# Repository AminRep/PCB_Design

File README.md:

# PCB_Design
Various PCB CAD models developed using KiCad software for educational and personal purposes.
## STM32 PCB Design
This is a custom PCB design for the microcontroller STM32F103C8T6, intended to assist in embedded systems studies. The design was realized from a detailed schematic using KiCad to the design of the PCB layout in a compact way. It provides a solid board on which to perform programming and prototyping with the STM32 processor, among other applications. Much attention was paid to ensuring that the design is easy for beginners to follow while still being highly functional.

## Self-Balancing Robot PCB
This PCB design is tailored for a self-balancing robot. It integrates key components like the L298N motor driver, MPU6050 gyroscope and accelerometer, and an Arduino Nano microcontroller. The layout provides a compact and efficient way to control motors, balancing algorithms, and sensor integration.

### Features:
* Motor Control: L298N driver to manage two DC motors.
* Sensor Input: MPU6050 for real-time balance adjustments.
* Microcontroller: Arduino Nano compatibility for seamless programming and control.
* Power Management: Includes regulators for stable operation.

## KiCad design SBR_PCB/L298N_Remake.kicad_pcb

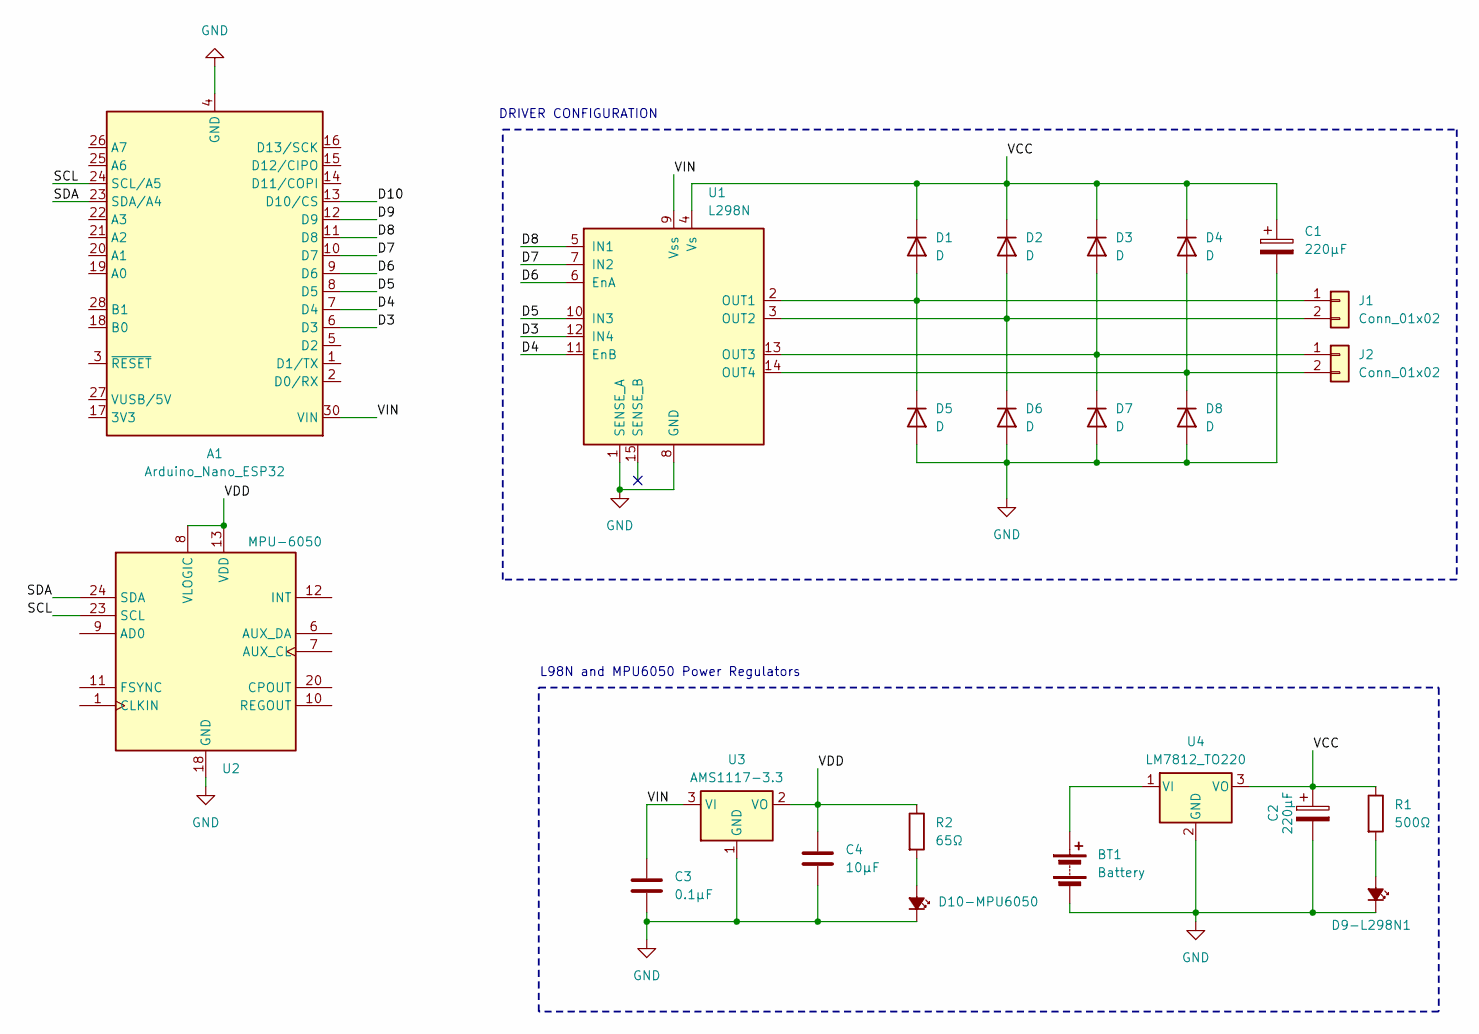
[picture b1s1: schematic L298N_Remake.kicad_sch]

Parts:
A1: Arduino_Nano_ESP32; Arduino_Nano
BT1: Battery; BatteryHolder_Bulgin_BX0036_1xC
C1, C2: 220µF; CP_Radial_D8.0mm_P2.50mm
C3: 0.1µF; C_Axial_L3.8mm_D2.6mm_P7.50mm_Horizontal
C4: 10µF; CP_Radial_D4.0mm_P1.50mm
D1, D2, D3, D4, D5, D6, D7, D8: D; D_A-405_P2.54mm_Vertical_AnodeUp
D9-L298N1, D10-MPU6050: LED_Small_Filled; LED_D3.0mm
J1, J2: Conn_01x02; TerminalBlock_Phoenix_MKDS-1,5-2-5.08_1x02_P5.08mm_Horizont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
R1: 500Ω; R_Axial_DIN0204_L3.6mm_D1.6mm_P7.62mm_Horizontal
R2: 65Ω; R_Axial_DIN0204_L3.6mm_D1.6mm_P5.08mm_Horizontal
U1: L298N; Multiwatt15_V_STM
U2: MPU-6050; InvenSense_QFN-24_4x4mm_P0.5mm
U3: AMS1117-3.3; SOT-223-3_TabPin2
U4: LM7812_TO220; TO-220-3_Vertical

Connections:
/D3: A1.6 (D3), U1.12 (IN4)
/D4: A1.7 (D4), U1.11 (EnB)
/D5: A1.8 (D5), U1.10 (IN3)
/D6: A1.9 (D6), U1.6 (EnA)
/D7: A1.10 (D7), U1.7 (IN2)
/D8: A1.11 (D8), U1.5 (IN1)
/D9: A1.12 (D9)
/D10: A1.13 (D10/CS)
/SCL: A1.24 (SCL/A5), U2.23 (SCL)
/SDA: A1.23 (SDA/A4), U2.24 (SDA)
/VCC: C1.1, C2.1, D1.1 (K), D2.1 (K), D3.1 (K), D4.1 (K), R1.1, U1.4 (Vs), U4.3 (VO)
/VDD: C4.1, R2.1, U2.8 (VLOGIC), U2.13 (VDD), U3.2 (VO)
/VIN: A1.30 (VIN), C3.1, U1.9 (Vss), U3.3 (VI)
GND: A1.4 (GND), A1.29 (GND), BT1.2 (-), C1.2, C2.2, C3.2, C4.2, D5.2 (A), D6.2 (A), D7.2 (A), D8.2 (A), D9-L298N1.1 (K), D10-MPU6050.1 (K), U1.1 (SENSE_A), U1.8 (GND), U2.18 (GND), U3.1 (GND), U4.2 (GND)
unnamed: BT1.1 (+), U4.1 (VI)
unnamed: D1.2 (A), D5.1 (K), J1.1, U1.2 (OUT1)
unnamed: D2.2 (A), D6.1 (K), J1.2, U1.3 (OUT2)
unnamed: D3.2 (A), D7.1 (K), J2.1, U1.13 (OUT3)
unnamed: D4.2 (A), D8.1 (K), J2.2, U1.14 (OUT4)
unnamed: D9-L298N1.2 (A), R1.2
unnamed: D10-MPU6050.2 (A), R2.2

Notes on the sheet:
L98N and MPU6050 Power Regulators
DRIVER CONFIGURATION

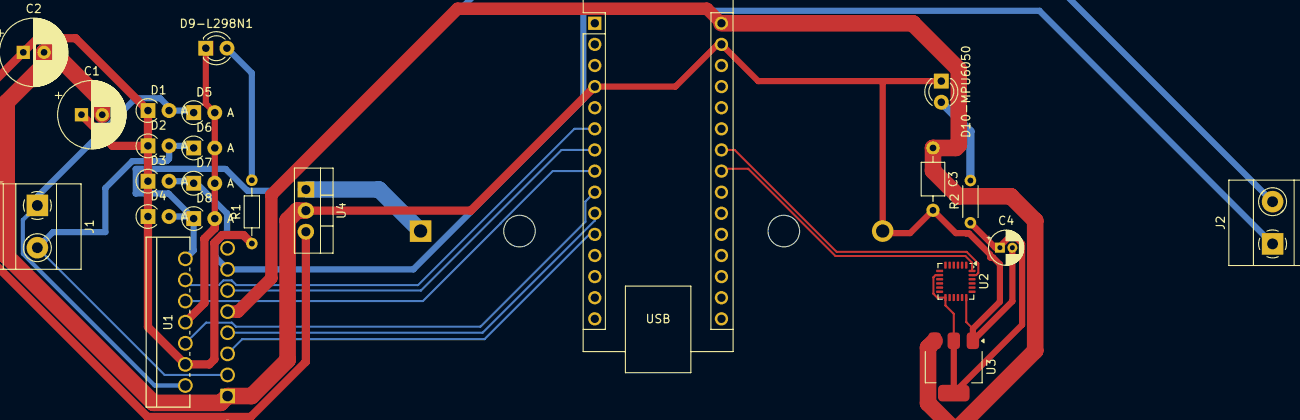
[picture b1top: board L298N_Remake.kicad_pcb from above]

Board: 2 copper layers, 24 parts (1 on the bottom side), 19 nets.

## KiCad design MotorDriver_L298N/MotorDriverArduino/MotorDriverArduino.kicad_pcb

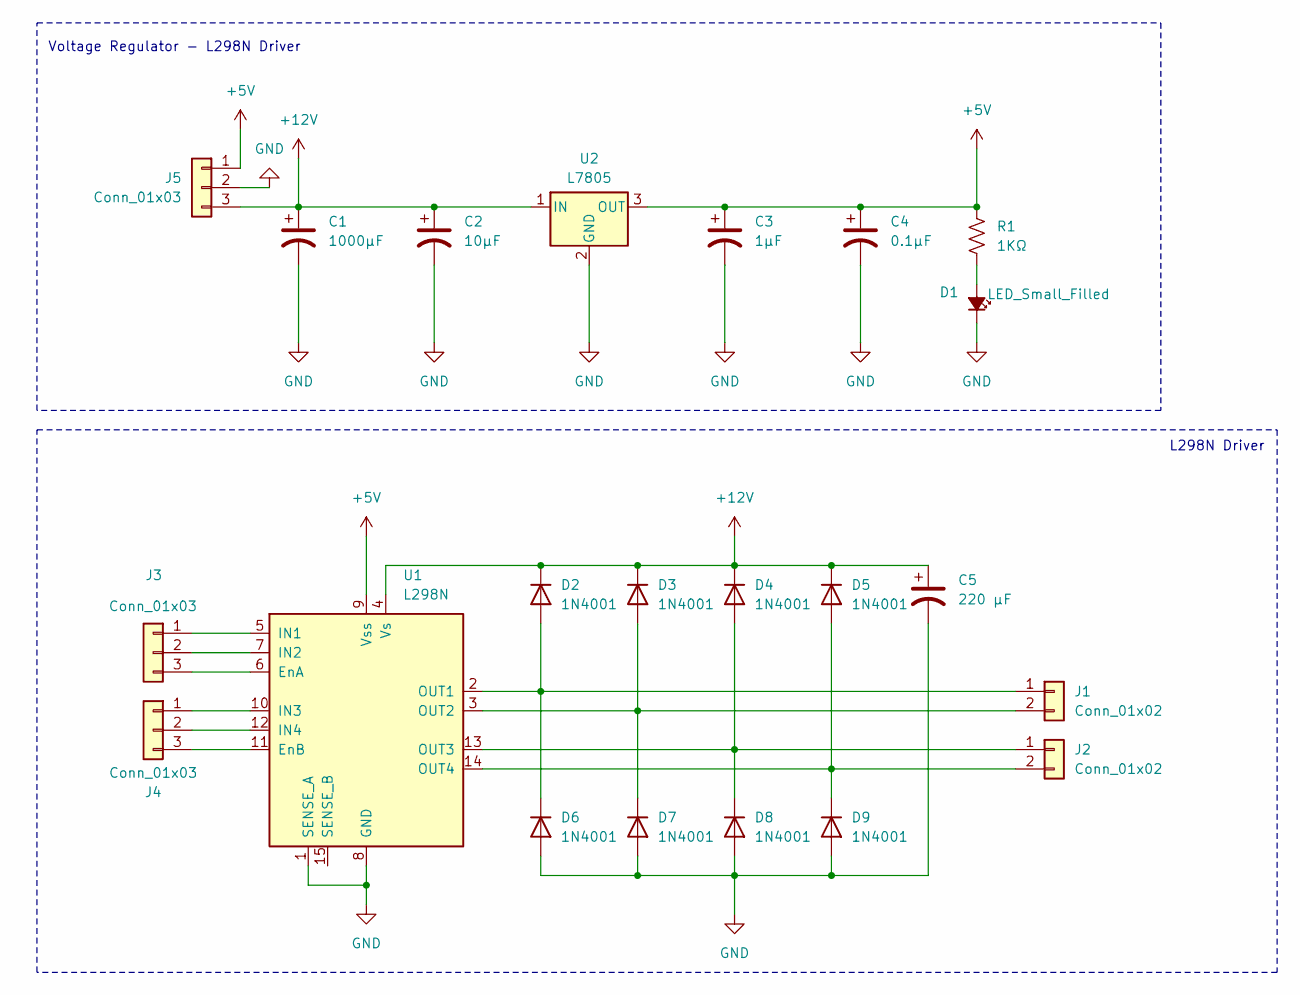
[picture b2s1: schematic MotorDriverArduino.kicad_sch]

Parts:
C1: 1000µF; CP_Radial_D5.0mm_P2.50mm
C2: 10µF; CP_Radial_D4.0mm_P1.50mm
C3: 1µF; C_0402_1005Metric
C4: 0.1µF; C_0402_1005Metric
C5: 220 µF; C_0805_2012Metric
D1: LED_Small_Filled; LED_0402_1005Metric_Pad0.77x0.64mm_HandSolder
D2, D3, D4, D5, D6, D7, D8, D9: 1N4001; D_0603_1608Metric_Pad1.05x0.95mm_HandSolder
J1, J2: Conn_01x02; TerminalBlock_Phoenix_MKDS-1,5-2_1x02_P5.00mm_Horizontal
J3, J4: Conn_01x03; PinSocket_1x03_P1.00mm_Vertical
J5: Conn_01x03; TerminalBlock_Phoenix_MKDS-1,5-3-5.08_1x03_P5.08mm_Horizont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
R1: 1KΩ; R_0805_2012Metric
U1: L298N; Multiwatt15_V_STM
U2: L7805; TO-262-3-1EP_Horizontal_TabDown

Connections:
+5V: C3.1, C4.1, J5.1, R1.1, U1.9 (Vss), U2.3 (OUT)
+12V: C1.1, C2.1, C5.1, D2.1 (K), D3.1 (K), D4.1 (K), D5.1 (K), J5.3, U1.4 (Vs), U2.1 (IN)
GND: C1.2, C2.2, C3.2, C4.2, C5.2, D1.1 (K), D6.2 (A), D7.2 (A), D8.2 (A), D9.2 (A), J5.2, U1.1 (SENSE_A), U1.8 (GND), U2.2 (GND)
unnamed: D1.2 (A), R1.2
unnamed: D2.2 (A), D6.1 (K), J1.1, U1.2 (OUT1)
unnamed: D3.2 (A), D7.1 (K), J1.2, U1.3 (OUT2)
unnamed: D4.2 (A), D8.1 (K), J2.1, U1.13 (OUT3)
unnamed: D5.2 (A), D9.1 (K), J2.2, U1.14 (OUT4)
unnamed: J3.1, U1.5 (IN1)
unnamed: J3.2, U1.7 (IN2)
unnamed: J3.3, U1.6 (EnA)
unnamed: J4.1, U1.10 (IN3)
unnamed: J4.2, U1.12 (IN4)
unnamed: J4.3, U1.11 (EnB)

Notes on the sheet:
L298N Driver
Voltage Regulator - L298N Driver

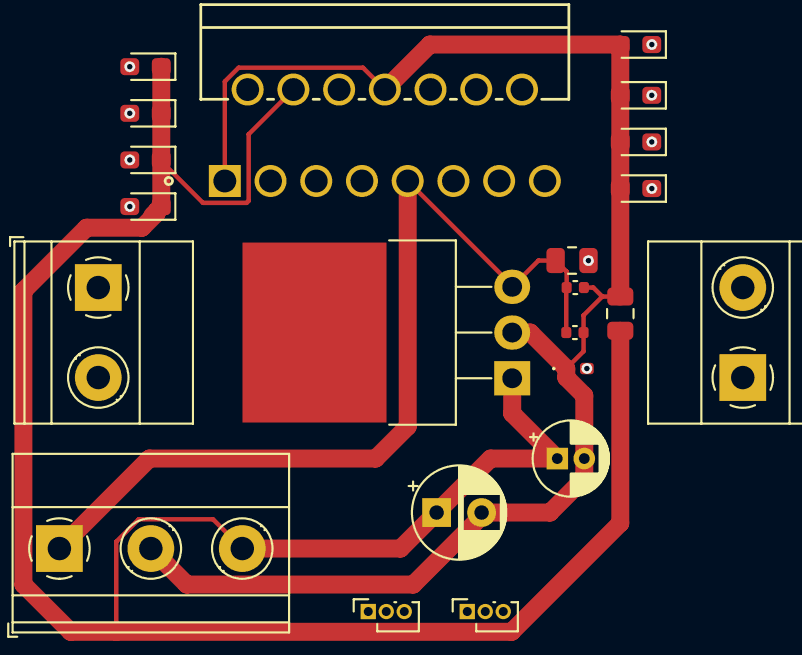
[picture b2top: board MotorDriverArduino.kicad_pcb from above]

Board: 4 copper layers, 22 parts (0 on the bottom side), 14 nets.

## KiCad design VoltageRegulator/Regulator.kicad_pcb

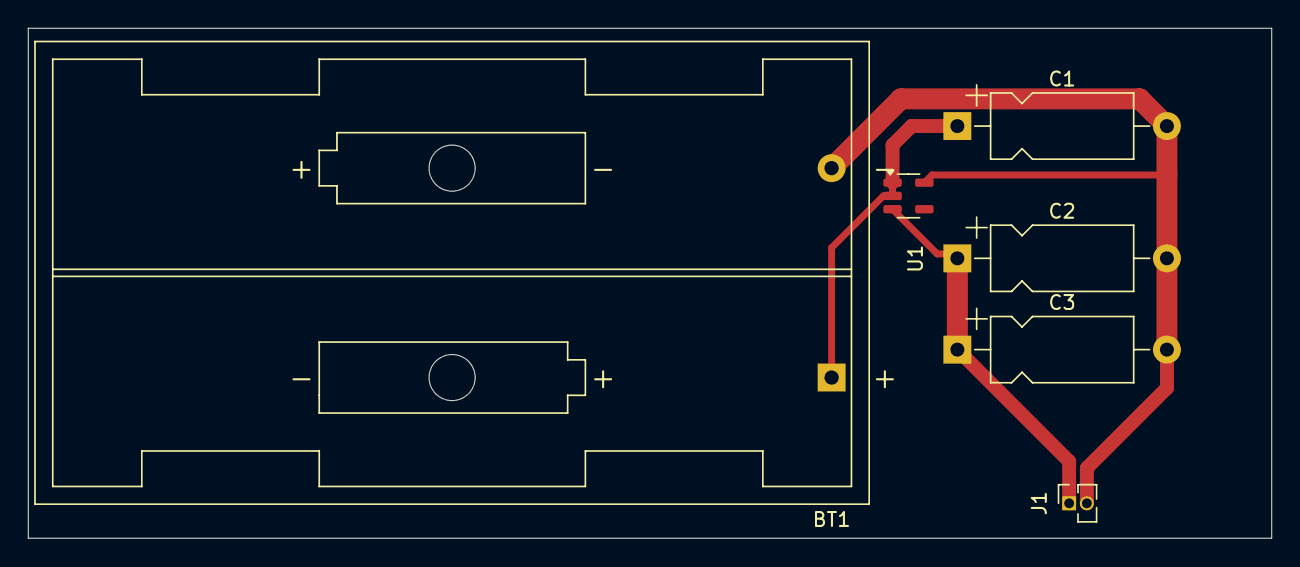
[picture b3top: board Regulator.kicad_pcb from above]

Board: 2 copper layers, 89.0 x 36.5 mm, 6 parts (0 on the bottom side), 3 nets.

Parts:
BT1: Battery; BatteryHolder_Keystone_2462_2xAA
C1, C2, C3: 10µF; CP_Axial_L10.0mm_D4.5mm_P15.00mm_Horizontal
J1: Conn_01x02; PinSocket_1x02_P1.27mm_Vertical
U1: MIC5219-3.3YMM; SOT-23-5

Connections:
+3V3: C2.1, C3.1, J1.1, U1.3 (OUT)
GND: BT1.2 (-), C1.2, C2.2, C3.2, J1.2, U1.5 (GND)
unnamed: BT1.1 (+), C1.1, U1.1 (EN), U1.2 (IN)

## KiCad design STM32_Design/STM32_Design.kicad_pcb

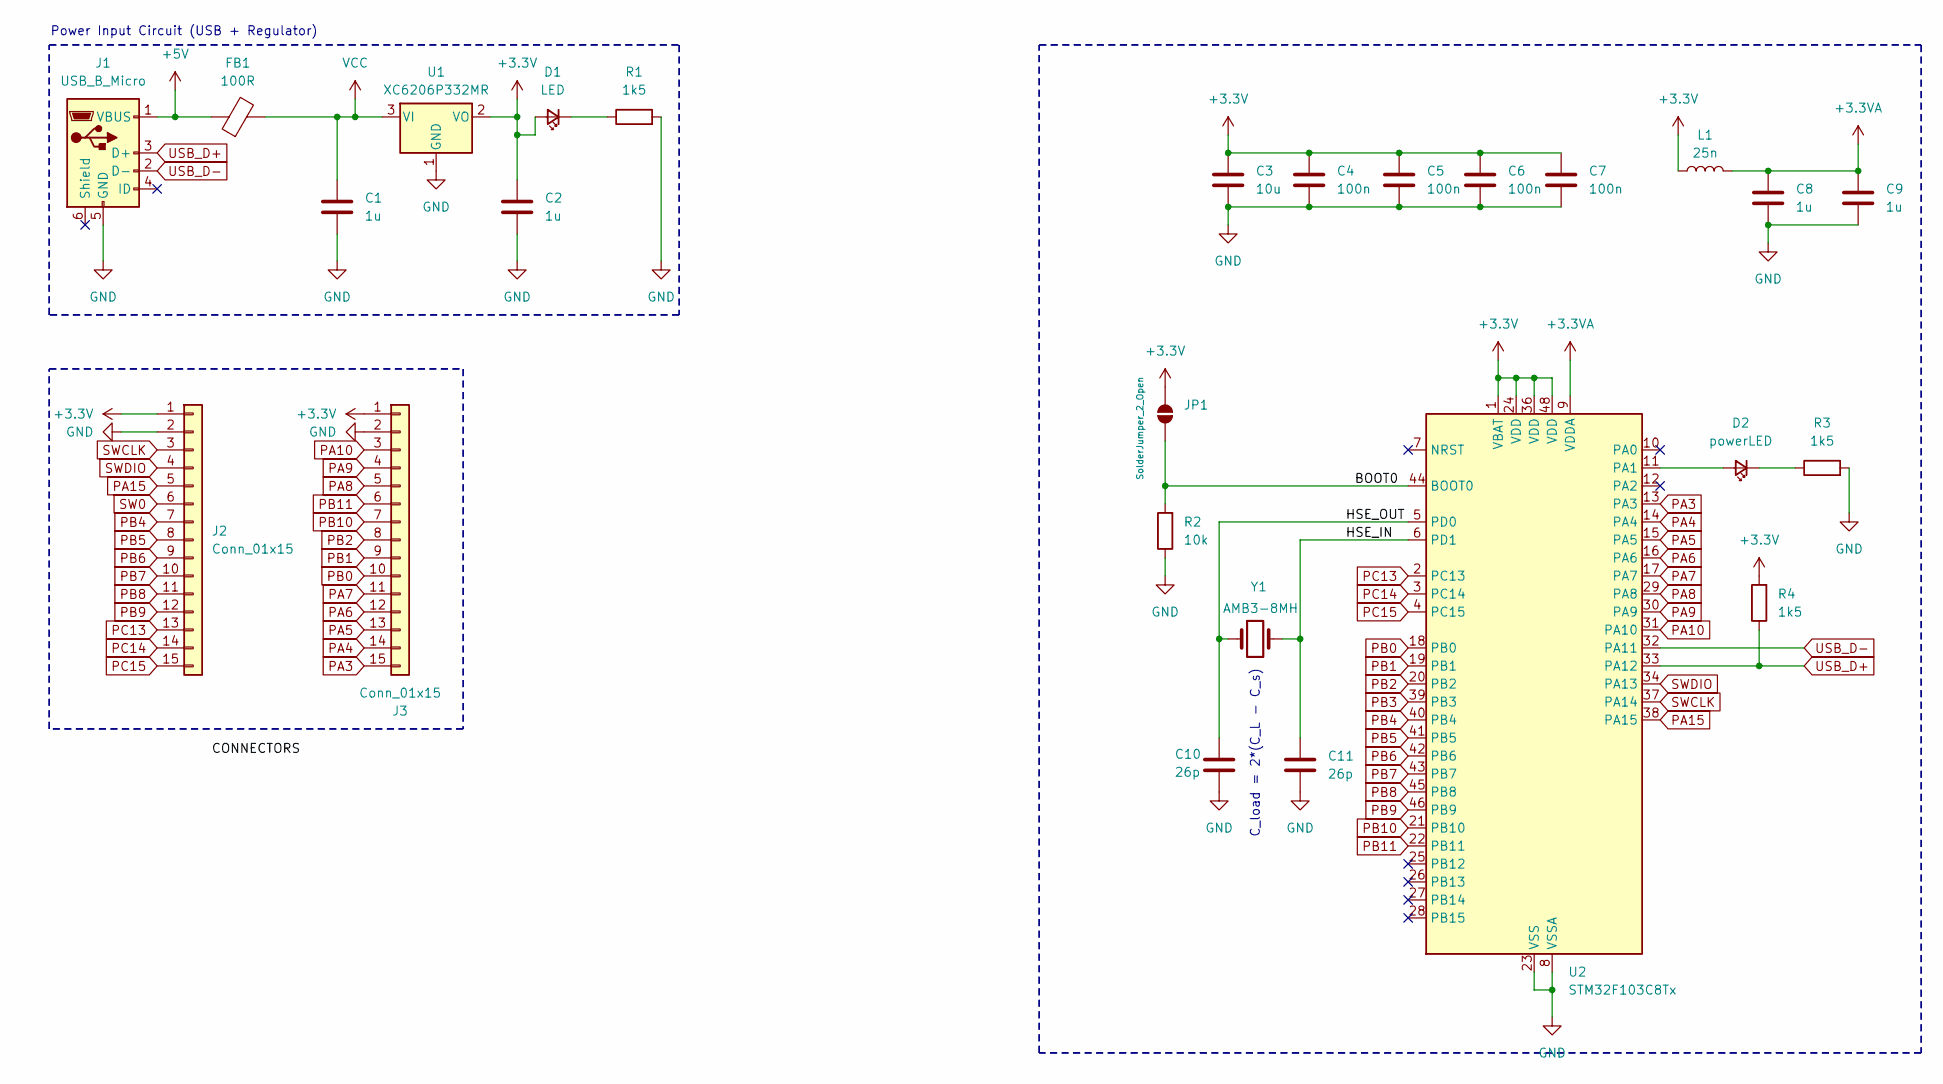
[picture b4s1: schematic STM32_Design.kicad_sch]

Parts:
C1, C2: 1u; C_0603_1608Metric
C3: 10u; C_0603_1608Metric
C4, C5, C6, C7: 100n; C_0402_1005Metric
C8, C9: 1u; C_0402_1005Metric
C10, C11: 26p; C_0402_1005Metric
D1: LED; LED_0201_0603Metric
D2: powerLED; LED_0201_0603Metric
FB1: 100R; L_0805_2012Metric
J1: USB_B_Micro; USB_Micro-B_Wuerth_629105150521
J2, J3: Conn_01x15; PinHeader_1x15_P2.54mm_Vertical
JP1: SolderJumper_2_Open; SolderJumper-2_P1.3mm_Open_Pad1.0x1.5mm
L1: 25n; L_01005_0402Metric
R1, R3: 1k5; R_0603_1608Metric
R2: 10k; R_0402_1005Metric
R4: 1k5; R_0402_1005Metric
U1: XC6206P332MR; SOT-23-3
U2: STM32F103C8Tx; LQFP-48_7x7mm_P0.5mm
Y1: AMB3-8MH; Crystal_SMD_5032-2Pin_5.0x3.2mm

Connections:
+3.3V: C2.1, C3.1, C4.1, C5.1, C6.1, C7.1, D1.2 (A), J2.1, J3.1, JP1.2 (B), L1.1, R4.2, U1.2 (VO), U2.1 (VBAT), U2.24 (VDD), U2.36 (VDD), U2.48 (VDD)
+3.3VA: C8.1, C9.1, L1.2, U2.9 (VDDA)
+5V: FB1.1, J1.1 (VBUS)
/BOOT0: JP1.1 (A), R2.2, U2.44 (BOOT0)
/HSE_IN: C11.1, U2.6 (PD1), Y1.2
/HSE_OUT: C10.1, U2.5 (PD0), Y1.1
GND: C1.2, C2.2, C3.2, C4.2, C5.2, C6.2, C7.2, C8.2, C9.2, C10.2, C11.2, J1.5 (GND), J2.2, J3.2, R1.2, R2.1, R3.2, U1.1 (GND), U2.8 (VSSA), U2.23 (VSS), U2.35 (VSS), U2.47 (VSS)
unnamed: D1.1 (K), R1.1
unnamed: D2.2 (A), U2.11 (PA1)
unnamed: D2.1 (K), R3.1
PA3: J3.15, U2.13 (PA3)
PA4: J3.14, U2.14 (PA4)
PA5: J3.13, U2.15 (PA5)
PA6: J3.12, U2.16 (PA6)
PA7: J3.11, U2.17 (PA7)
PA8: J3.5, U2.29 (PA8)
PA9: J3.4, U2.30 (PA9)
PA10: J3.3, U2.31 (PA10)
PA15: J2.5, U2.38 (PA15)
PB0: J3.10, U2.18 (PB0)
PB1: J3.9, U2.19 (PB1)
PB2: J3.8, U2.20 (PB2)
PB3: U2.39 (PB3)
PB4: J2.7, U2.40 (PB4)
PB5: J2.8, U2.41 (PB5)
PB6: J2.9, U2.42 (PB6)
PB7: J2.10, U2.43 (PB7)
PB8: J2.11, U2.45 (PB8)
PB9: J2.12, U2.46 (PB9)
PB10: J3.7, U2.21 (PB10)
PB11: J3.6, U2.22 (PB11)
PC13: J2.13, U2.2 (PC13)
PC14: J2.14, U2.3 (PC14)
PC15: J2.15, U2.4 (PC15)
SW0: J2.6
SWCLK: J2.3, U2.37 (PA14)
SWDIO: J2.4, U2.34 (PA13)
USB_D+: J1.3 (D+), R4.1, U2.33 (PA12)
USB_D-: J1.2 (D-), U2.32 (PA11)
VCC: C1.1, FB1.2, U1.3 (VI)

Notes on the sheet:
Power Input Circuit (USB + Regulator)
C_load = 2*(C_L - C_s)

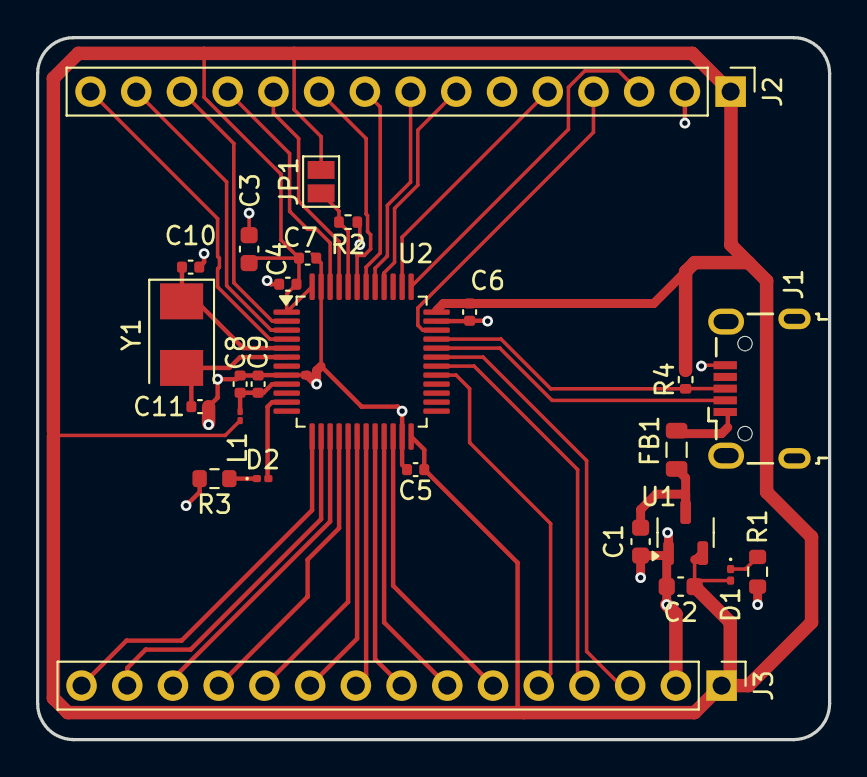
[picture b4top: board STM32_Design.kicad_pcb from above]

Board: 2 copper layers, 44.0 x 39.0 mm, 26 parts (0 on the bottom side), 38 nets.

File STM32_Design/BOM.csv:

"Id";"Designator";"Footprint";"Quantity";"Designation";"Supplier and ref";
1;"L1";"L_01005_0402Metric";1;"25n";;;
2;"Y1";"Crystal_SMD_5032-2Pin_5.0x3.2mm";1;"AMB3-8MH";;;
3;"U2";"LQFP-48_7x7mm_P0.5mm";1;"STM32F103C8Tx";;;
4;"U1";"SOT-23-3";1;"XC6206P332MR";;;
5;"R4";"R_0402_1005Metric";1;"1k5";;;
6;"R3,R1";"R_0603_1608Metric";2;"1k5";;;
7;"R2";"R_0402_1005Metric";1;"10k";;;
8;"J3,J2";"PinHeader_1x15_P2.54mm_Vertical";2;"Conn_01x15";;;
9;"J1";"USB_Micro-B_Wuerth_629105150521";1;"USB_B_Micro";;;
10;"FB1";"L_0805_2012Metric";1;"100R";;;
11;"D2";"LED_0201_0603Metric";1;"powerLED";;;
12;"D1";"LED_0201_0603Metric";1;"LED";;;
13;"C11,C10";"C_0402_1005Metric";2;"26p";;;
14;"C9,C8";"C_0402_1005Metric";2;"1u";;;
15;"C7,C6,C5,C4";"C_0402_1005Metric";4;"100n";;;
16;"C3";"C_0603_1608Metric";1;"10u";;;
17;"C2,C1";"C_0603_1608Metric";2;"1u";;;

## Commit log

2025-01-21 STM32,SRB Robot, L298N, Voltage Rgulator
2025-01-21 images are added
2025-01-21 Rename SRB Board Render.png to SRB_Board_Render.png
